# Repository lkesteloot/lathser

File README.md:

# Lathser

By Lawrence Kesteloot and Kurt Schaefer.

(Pronounced *lathe-zer*.) This project lets you cut a 3D shape using a 2D laser
cutter by rotating the piece as it's being cut.

The stock piece (an acrylic or wooden rod) is held and rotated by this machine
built by Kurt:

You can read the [full writeup](http://retrotechjournal.com/2015/09/01/cutting-3d-shapes-on-a-laser-cutter/).

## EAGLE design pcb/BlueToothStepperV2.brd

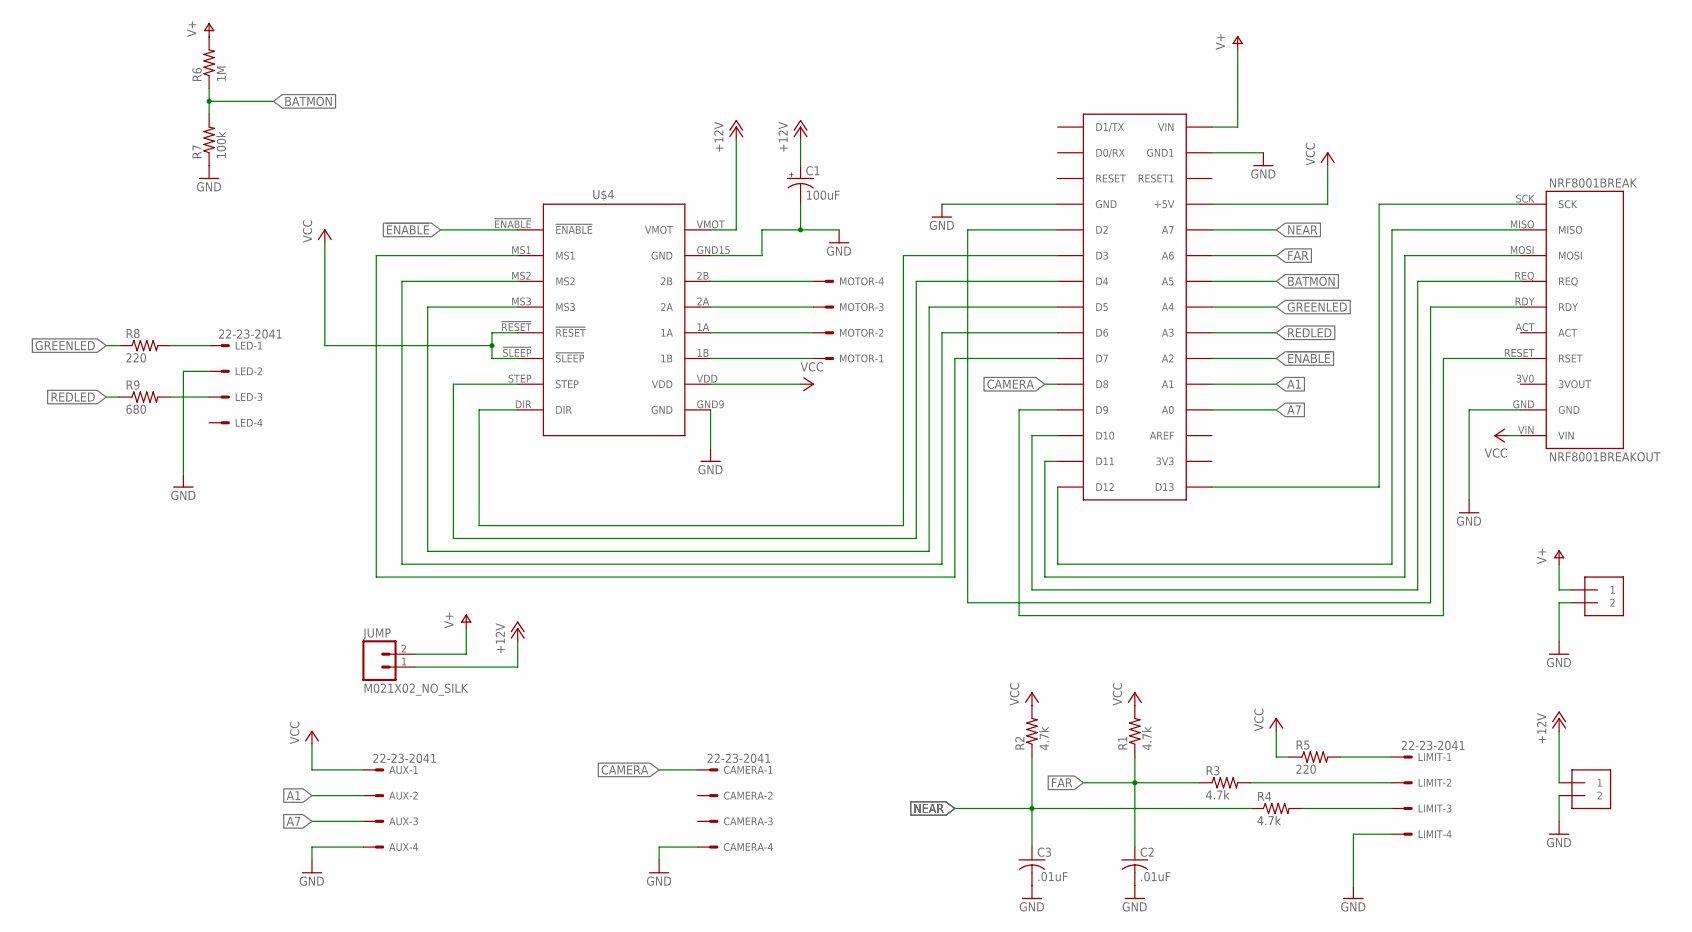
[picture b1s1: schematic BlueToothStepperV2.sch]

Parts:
7VOLT, 12VOLT: 1X2-3.5MM
AUX: 22-23-2041
C1: 100uF; E3,5-8
C2, C3: .01uF; C050-030X075
CAMERA: 22-23-2041
JUMP: M021X02_NO_SILK; 1X02_NO_SILK
LED: 22-23-2041
LIMIT: 22-23-2041
MOTOR: 22-23-2041
NANO: ARDUINONANO; PDIP-32
NRF8001BREAK: NRF8001BREAKOUT; BREAKOUTV2
R1, R2, R3, R4: 4.7k; 0207/9
R5, R8: 220; 0207/9
R6: 1M; 0207/9
R7: 100k; 0207/9
R9: 680; 0207/9
U$4: STEPPER1616PINV2; STEPPER16PINV2

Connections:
!ENABLE: NANO.A2, U$4.!ENABLE
+12V: 12VOLT.1, C1.+, JUMP.1, U$4.VMOT
A1: AUX.2, NANO.A1
A7: AUX.3, NANO.A0
BATMON: NANO.A5, R6.1, R7.2
CAMERA: CAMERA.1, NANO.D8
FAR: C2.1, NANO.A6, R1.1, R3.1
GND: 7VOLT.2, 12VOLT.2, AUX.4, C1.-, C2.2, C3.2, CAMERA.4, LED.2, LIMIT.4, NANO.GND, NANO.GND1, NRF8001BREAK.GND, R7.1, U$4.GND9 (GND), U$4.GND15 (GND)
GREENLED: NANO.A4, R8.1
unnamed: NANO.D13, NRF8001BREAK.SCK
unnamed: NANO.D12, NRF8001BREAK.MISO
unnamed: NANO.D11, NRF8001BREAK.MOSI
unnamed: NANO.D10, NRF8001BREAK.REQ
unnamed: NANO.D2, NRF8001BREAK.RDY
unnamed: NANO.D9, NRF8001BREAK.RESET (RSET)
unnamed: LIMIT.1, R5.2
unnamed: NANO.D4, U$4.STEP
unnamed: NANO.D3, U$4.DIR
unnamed: MOTOR.4, U$4.2B
unnamed: LIMIT.2, R3.2
unnamed: MOTOR.3, U$4.2A
unnamed: MOTOR.2, U$4.1A
unnamed: MOTOR.1, U$4.1B
unnamed: LIMIT.3, R4.2
unnamed: NANO.D5, U$4.MS3
unnamed: NANO.D6, U$4.MS2
unnamed: NANO.D7, U$4.MS1
unnamed: LED.1, R8.2
unnamed: LED.3, R9.2
NEAR: C3.1, NANO.A7, R2.1, R4.1
REDLED: NANO.A3, R9.1
V+: 7VOLT.1, JUMP.2, NANO.VIN, R6.2
VCC: AUX.1, NANO.+5V, NRF8001BREAK.VIN, R1.2, R2.2, R5.1, U$4.!RESET, U$4.!SLEEP, U$4.VDD

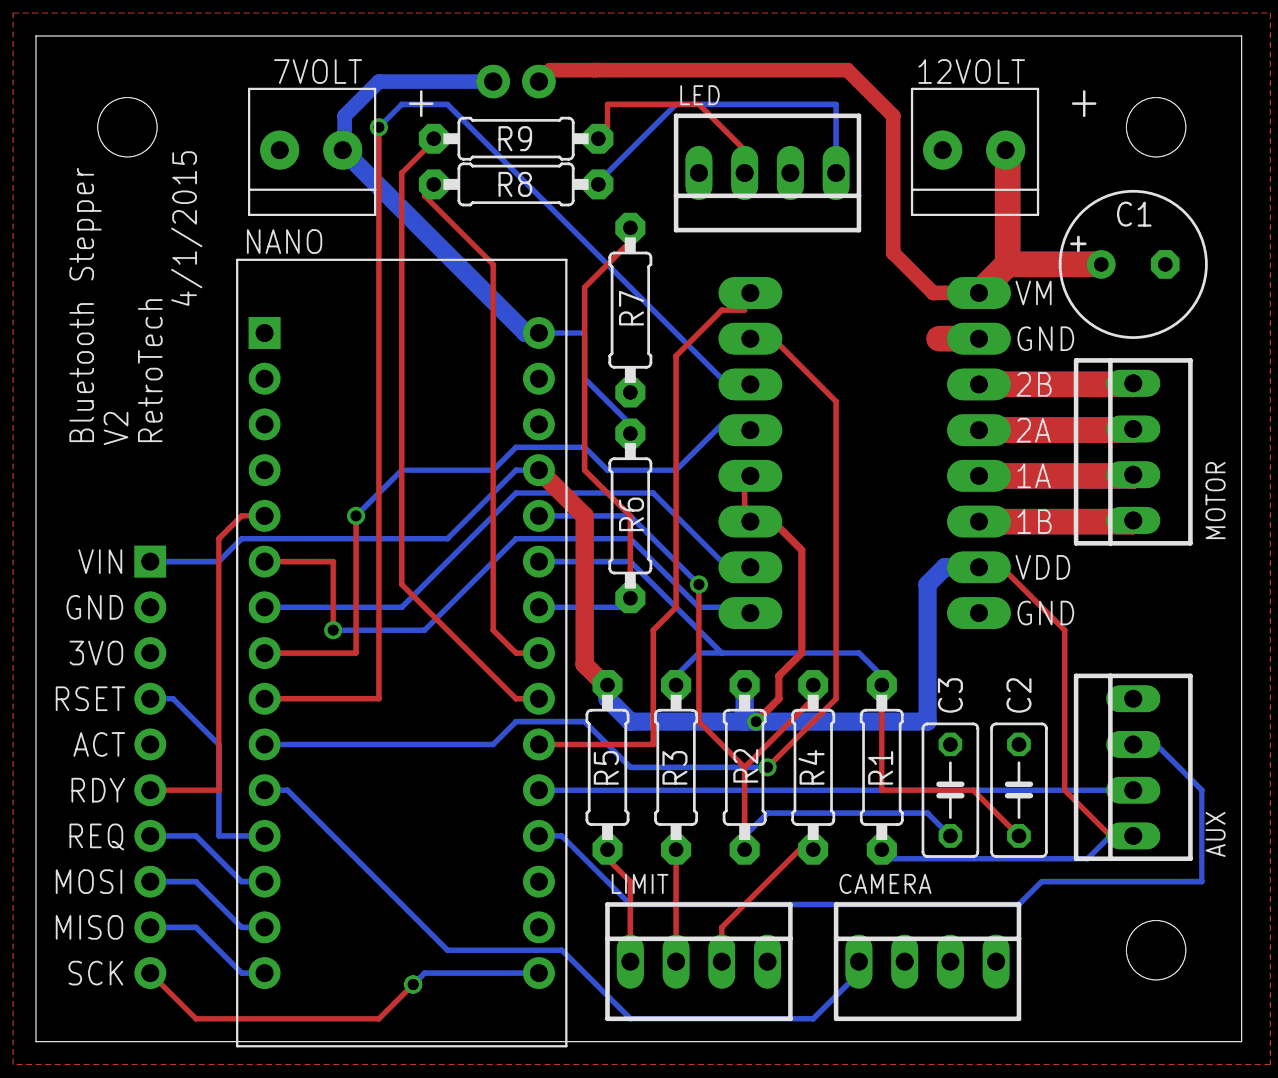
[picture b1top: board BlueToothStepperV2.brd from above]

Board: 2 copper layers, 67.0 x 55.9 mm, 26 parts (0 on the bottom side), 33 nets.

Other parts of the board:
U$1, U$5, U$6: STAND-OFF

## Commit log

2014-11-27 Initial commit.
2014-11-27 Draw shape.
2014-11-27 Generate rotating gif.
2014-11-27 Clean up.
2014-11-27 Support multiple meshes.
2014-12-30 Generate SVG file.
2015-01-29 Center more consistently.
2015-01-29 Support multiple paths.
2015-01-29 Add README.
2015-01-29 Apply license.
2015-01-29 Remove images2gif.
2015-01-29 Add photo of machine.
2015-02-04 Clean up code.
2015-02-04 Handle open paths.
2015-02-04 Spiral in.
2015-02-04 Add kerf.
2015-02-09 Add knight.json data file.
2015-02-09 Try to fix location of spiral line.
2015-02-09 Add lighting pass.
2015-02-11 Fix horizontal position of shade lines.
2015-02-12 Generate a single path.
2015-02-12 Larger margin; increase resolution.
2015-02-26 Add device code to the tree
    This is just the rough first cut of the code that drives the Arduino,
    and the ATTiny85 laser detection code.
2015-02-27 Add the initial illustrator CS5 version of the indexing rig
2015-03-05 Can generate .vector files for ctrl-cut.
2015-03-06 Can generate raw Epilog files directly.
2015-03-12 Fix up Fusion output.
2015-03-19 Add the ability to download a sequence and step though it under blue tooth and thermal control
2015-03-22 First pass at the ios app.
2015-03-22 Make it so we track the thermal sensor, and communicate back and forth with the board from the ios app.
2015-03-23 Make it so the device sequence comes from the positions array.
2015-03-23 Make it so we clear the thermal color when we are not connected to the device.
2015-03-23 Make it so we send a thermal reading right away after getting a sequence so the thermal indicator also acts as a ready to run light.
2015-03-27 Add explicit heat sensor and time waster functions.
2015-03-27 Write thetas.txt file.
2015-03-28 Change escape to plain character
2015-03-28 Add an app icon. Move the thermal sensor out into it's own view class. Hard wire a new sequence in.
2015-03-28 Add the illustrator file for the icon
2015-03-28 remove the .png restriction and add in all the images from the iosApp that were getting ignored.
2015-03-28 Update the licensing and rename some files.
2015-03-28 Add eagle cad ignore files in prep for adding PCB to lathser
2015-04-15 Reduce ROUGH_EXTRA_IN so that it doesn't fill out the image completely.
2015-04-15 Rotate model in 3D if around the wrong axis.
2015-04-16 Try DNA model.
2015-04-16 Split cuts differently on Epilog.
2015-04-16 Cut out on top; faster waster circles.
2015-04-21 Change outline so it outputs thetas as a deep link compatible with the app.
2015-05-08 Add raster output.
2015-05-09 Start web version.
2015-05-09 Add JavaScript rendering.
2015-05-09 Support for deep linking of sequences to get them into the app easily.
2015-05-10 Make it so communications to the arduino has confirmations, and an async block based communications interface. Add new thermal switch testing code as well.
2015-05-10 Make the sequencer faster at dealing with no connection.
2015-05-10 Update the thermal sensor when you're not connected.
2015-05-10 Handle disabling/enabling the send button. Adjust some comments.
2015-05-10 Rename the sequencer to just be a bluetooth peripheral.
2015-05-10 Make it so extra acks do not crash the app.
2015-05-10 Initial cut of the schematic V2 of the board.
2015-05-10 Make the log a little less noisy.
2015-05-10 Simplify paths in JS.
2015-05-10 Generate outline of model in web version.
2015-05-10 Transform paths to final cut positions.
2015-05-11 Generate PRN file from web.
2015-05-11 Add base in web.
2015-05-11 Add timing to logging.
2015-05-11 Add kerf in web.
2015-05-14 Add shade and clear top.
2015-05-14 Add two extra positions in the default sequence for raster passes. Add a response string method to the Arduino code.
2015-05-14 Do multiple passes and angles.
2015-05-14 Get DPI right.
2015-05-14 Add SVG support in web.
2015-05-14 Add support for %g. Not really tested.
2015-05-14 Add heat sensor cut and time waster cut.
2015-05-14 Try DNA.
2015-06-11 Add 3D view.
2015-06-11 Can do raster pass in JS.
2015-09-01 Add link to Kurt's blog post.
2018-11-05 Update NOTES.

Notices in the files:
parts and their libraries:
SparkFun-Electromechanical: Licensing: Creative Commons ShareAlike 4.0 International - https://creativecommons.org/licenses/by-sa/4.0
